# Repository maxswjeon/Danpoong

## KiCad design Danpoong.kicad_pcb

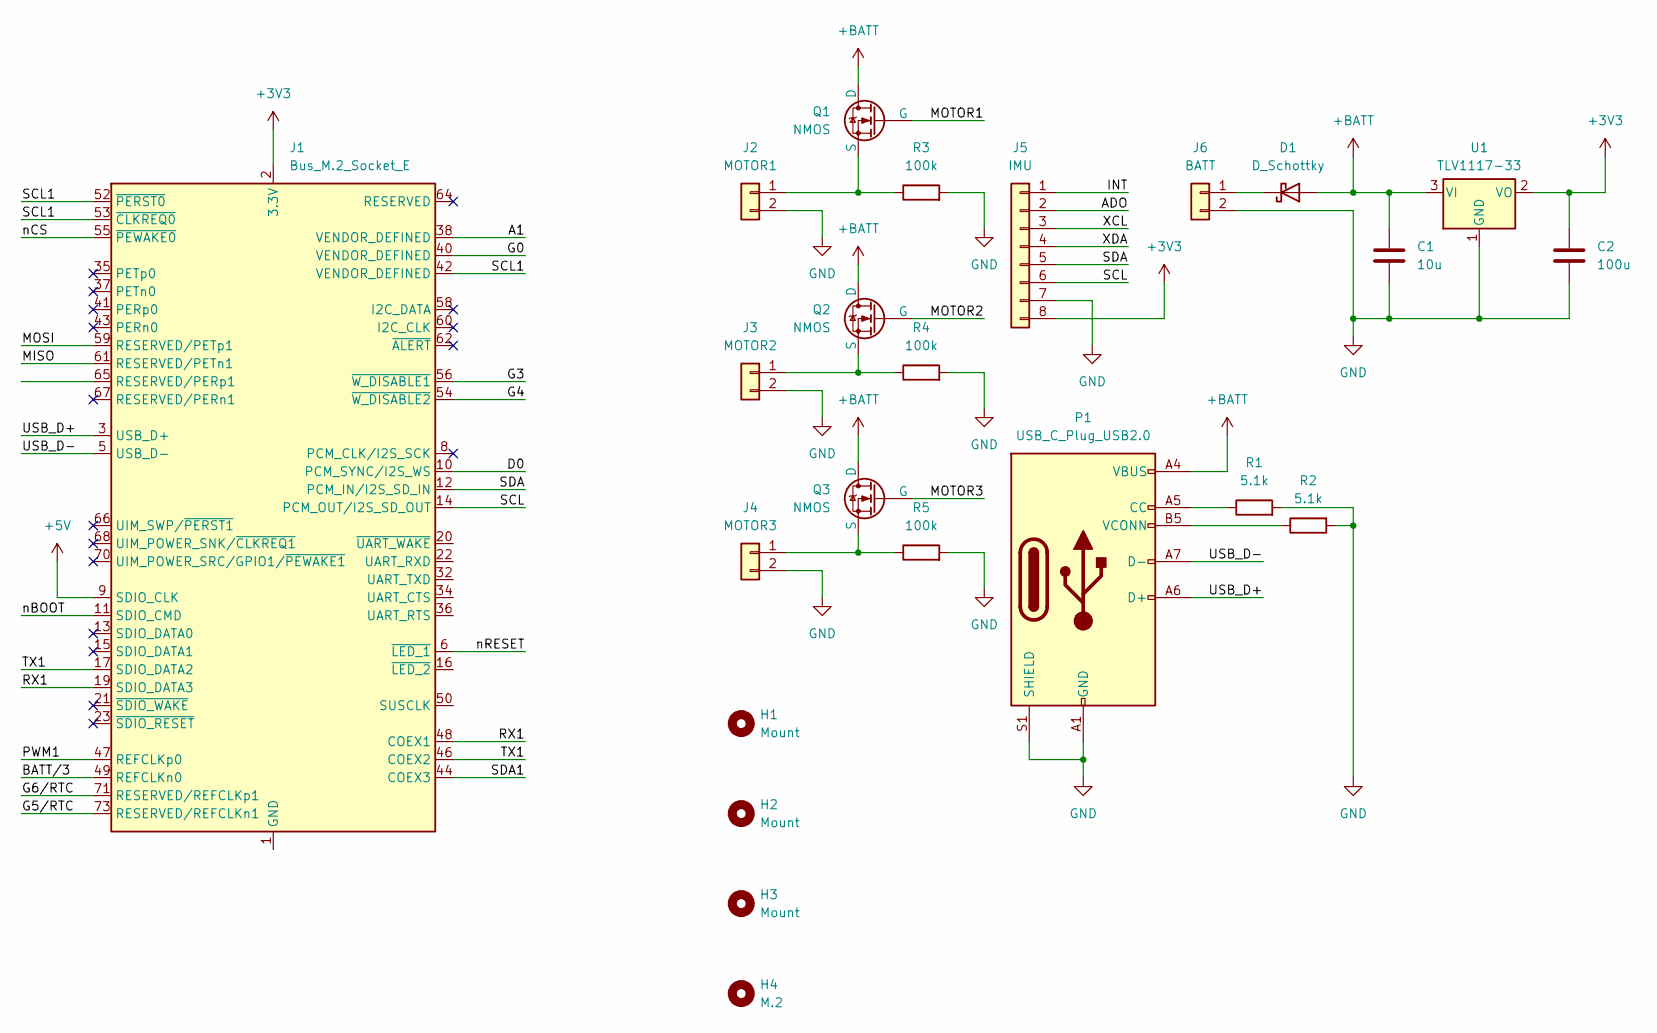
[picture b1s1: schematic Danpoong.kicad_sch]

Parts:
C1: 10u; C_0603_1608Metric
C2: 100u; C_0603_1608Metric
D1: D_Schottky; PMEG2020EPK315
H1, H2, H3: Mount; MountingHole_2.2mm_M2_DIN965
H4: M.2; MountingHole_2.2mm_M2_DIN965
J1: Bus_M.2_Socket_E; MDT275E03001
J2: MOTOR1; PinHeader_1x02_P1.00mm_Vertical
J3: MOTOR2; PinHeader_1x02_P1.00mm_Vertical
J4: MOTOR3; PinHeader_1x02_P1.00mm_Vertical
J5: IMU; PinSocket_1x08_P2.54mm_Vertical
J6: BATT; PinHeader_1x02_P1.27mm_Vertical
P1: USB_C_Plug_USB2.0; USB_C_Receptacle_GCT_USB4085
Q1, Q2, Q3: NMOS; TSOT-23
R1, R2: 5.1k; R_0603_1608Metric
R3, R4, R5: 100k; R_0603_1608Metric
U1: TLV1117-33; SOT-223-3_TabPin2

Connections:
+3V3: C2.1, J1.2 (3.3V), J1.4 (3.3V), J1.72 (3.3V), J1.74 (3.3V), J5.8, U1.2 (VO)
+5V: J1.9 (SDIO_CLK)
+BATT: C1.1, D1.2 (A), P1.A4 (VBUS), P1.A9 (VBUS), P1.B4 (VBUS), P1.B9 (VBUS), Q1.1 (D), Q2.1 (D), Q3.1 (D), U1.3 (VI)
/A1: J1.38 (VENDOR_DEFINED)
/ADO: J5.2
/BATT/3: J1.49 (REFCLKn0)
/D0: J1.10 (PCM_SYNC/I2S_WS)
/G0: J1.40 (VENDOR_DEFINED)
/G3: J1.56 (~W_DISABLE1)
/G4: J1.54 (~W_DISABLE2)
/G5/RTC: J1.73 (RESERVED/REFCLKn1)
/G6/RTC: J1.71 (RESERVED/REFCLKp1)
/INT: J5.1
/MISO: J1.61 (RESERVED/PETn1)
/MOSI: J1.59 (RESERVED/PETp1)
/MOTOR1: Q1.2 (G)
/MOTOR2: Q2.2 (G)
/MOTOR3: Q3.2 (G)
/PWM1: J1.47 (REFCLKp0)
/RX1: J1.19 (SDIO_DATA3), J1.48 (COEX1)
/SCL: J1.14 (PCM_OUT/I2S_SD_OUT), J5.6
/SCL1: J1.42 (VENDOR_DEFINED), J1.52 (~PERST0), J1.53 (~CLKREQ0)
/SDA: J1.12 (PCM_IN/I2S_SD_IN), J5.5
/SDA1: J1.44 (COEX3)
/TX1: J1.17 (SDIO_DATA2), J1.46 (COEX2)
/USB_D+: J1.3 (USB_D+), P1.A6 (D+)
/USB_D-: J1.5 (USB_D-), P1.A7 (D-)
/XCL: J5.3
/XDA: J5.4
/nBOOT: J1.11 (SDIO_CMD)
/nCS: J1.55 (~PEWAKE0)
/nRESET: J1.6 (~LED_1)
GND: C1.2, C2.2, J2.2, J3.2, J4.2, J5.7, J6.2, P1.A1 (GND), P1.A12 (GND), P1.B1 (GND), P1.B12 (GND), P1.S1 (SHIELD), R1.2, R2.2, R3.2, R4.2, R5.2, U1.1 (GND)
unnamed: D1.1 (K), J6.1
unnamed: J1.1 (GND), J1.7 (GND), J1.18 (GND), J1.33 (GND), J1.39 (GND), J1.45 (GND), J1.51 (GND), J1.57 (GND), J1.63 (GND), J1.69 (GND), J1.75 (GND)
unnamed: J2.1, Q1.3 (S), R3.1
unnamed: J3.1, Q2.3 (S), R4.1
unnamed: J4.1, Q3.3 (S), R5.1
unnamed: P1.A5 (CC), R1.1
unnamed: P1.B5 (VCONN), R2.1

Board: 2 copper layers, 23 parts (0 on the bottom side), 17 nets, no tracks yet.

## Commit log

2024-02-18 chore: initialize repository
2024-02-18 wip: start development
